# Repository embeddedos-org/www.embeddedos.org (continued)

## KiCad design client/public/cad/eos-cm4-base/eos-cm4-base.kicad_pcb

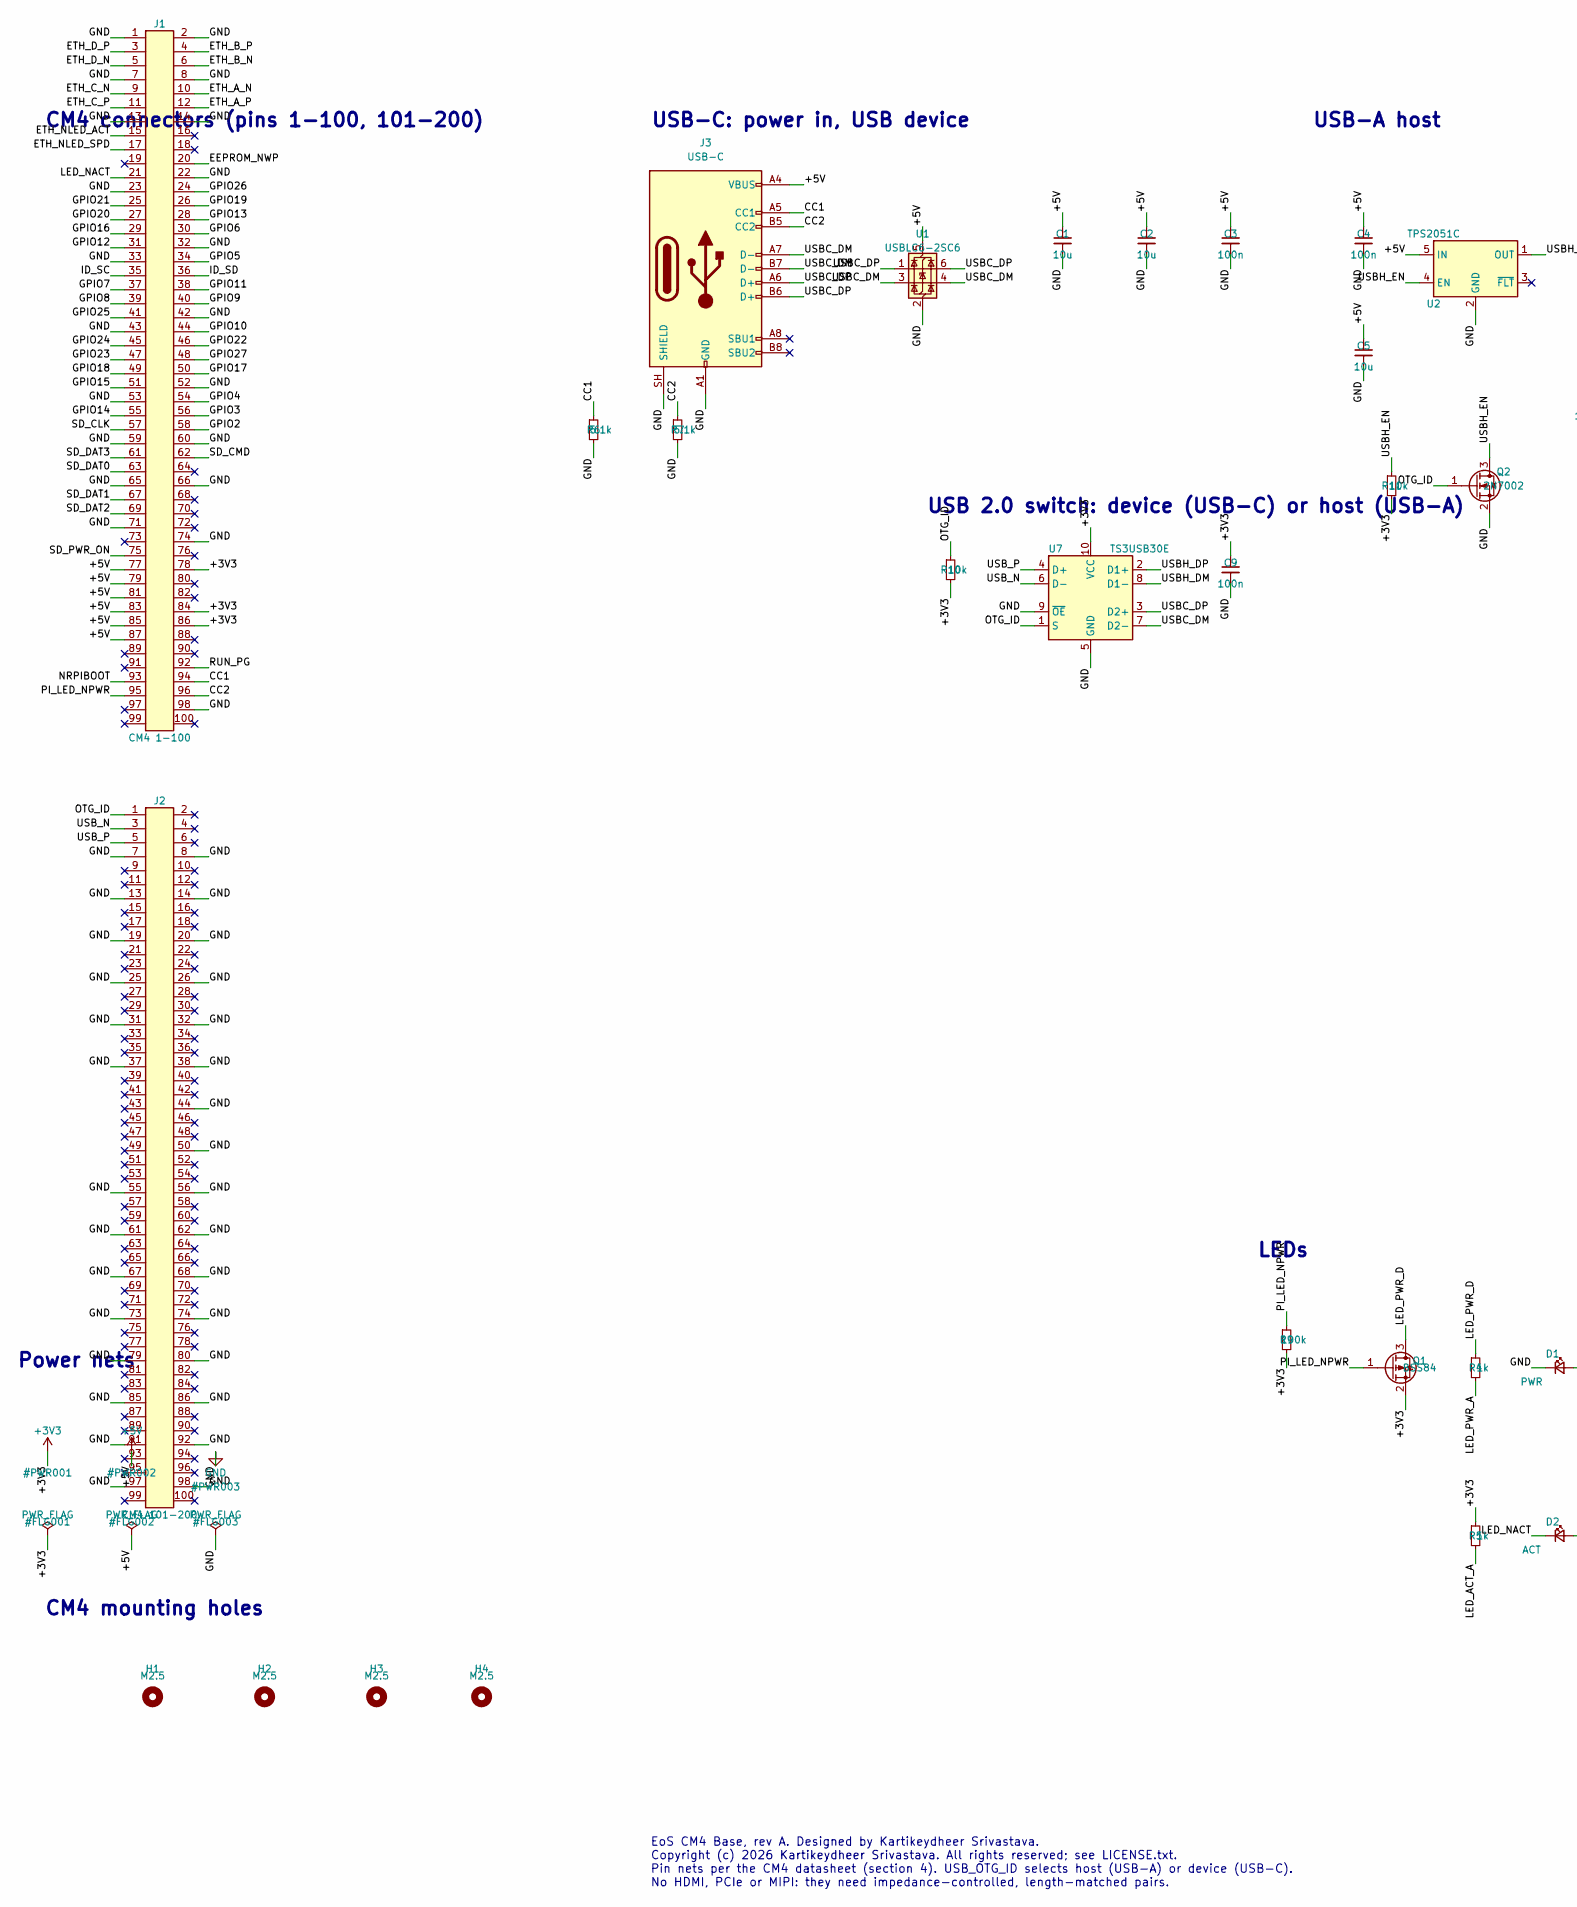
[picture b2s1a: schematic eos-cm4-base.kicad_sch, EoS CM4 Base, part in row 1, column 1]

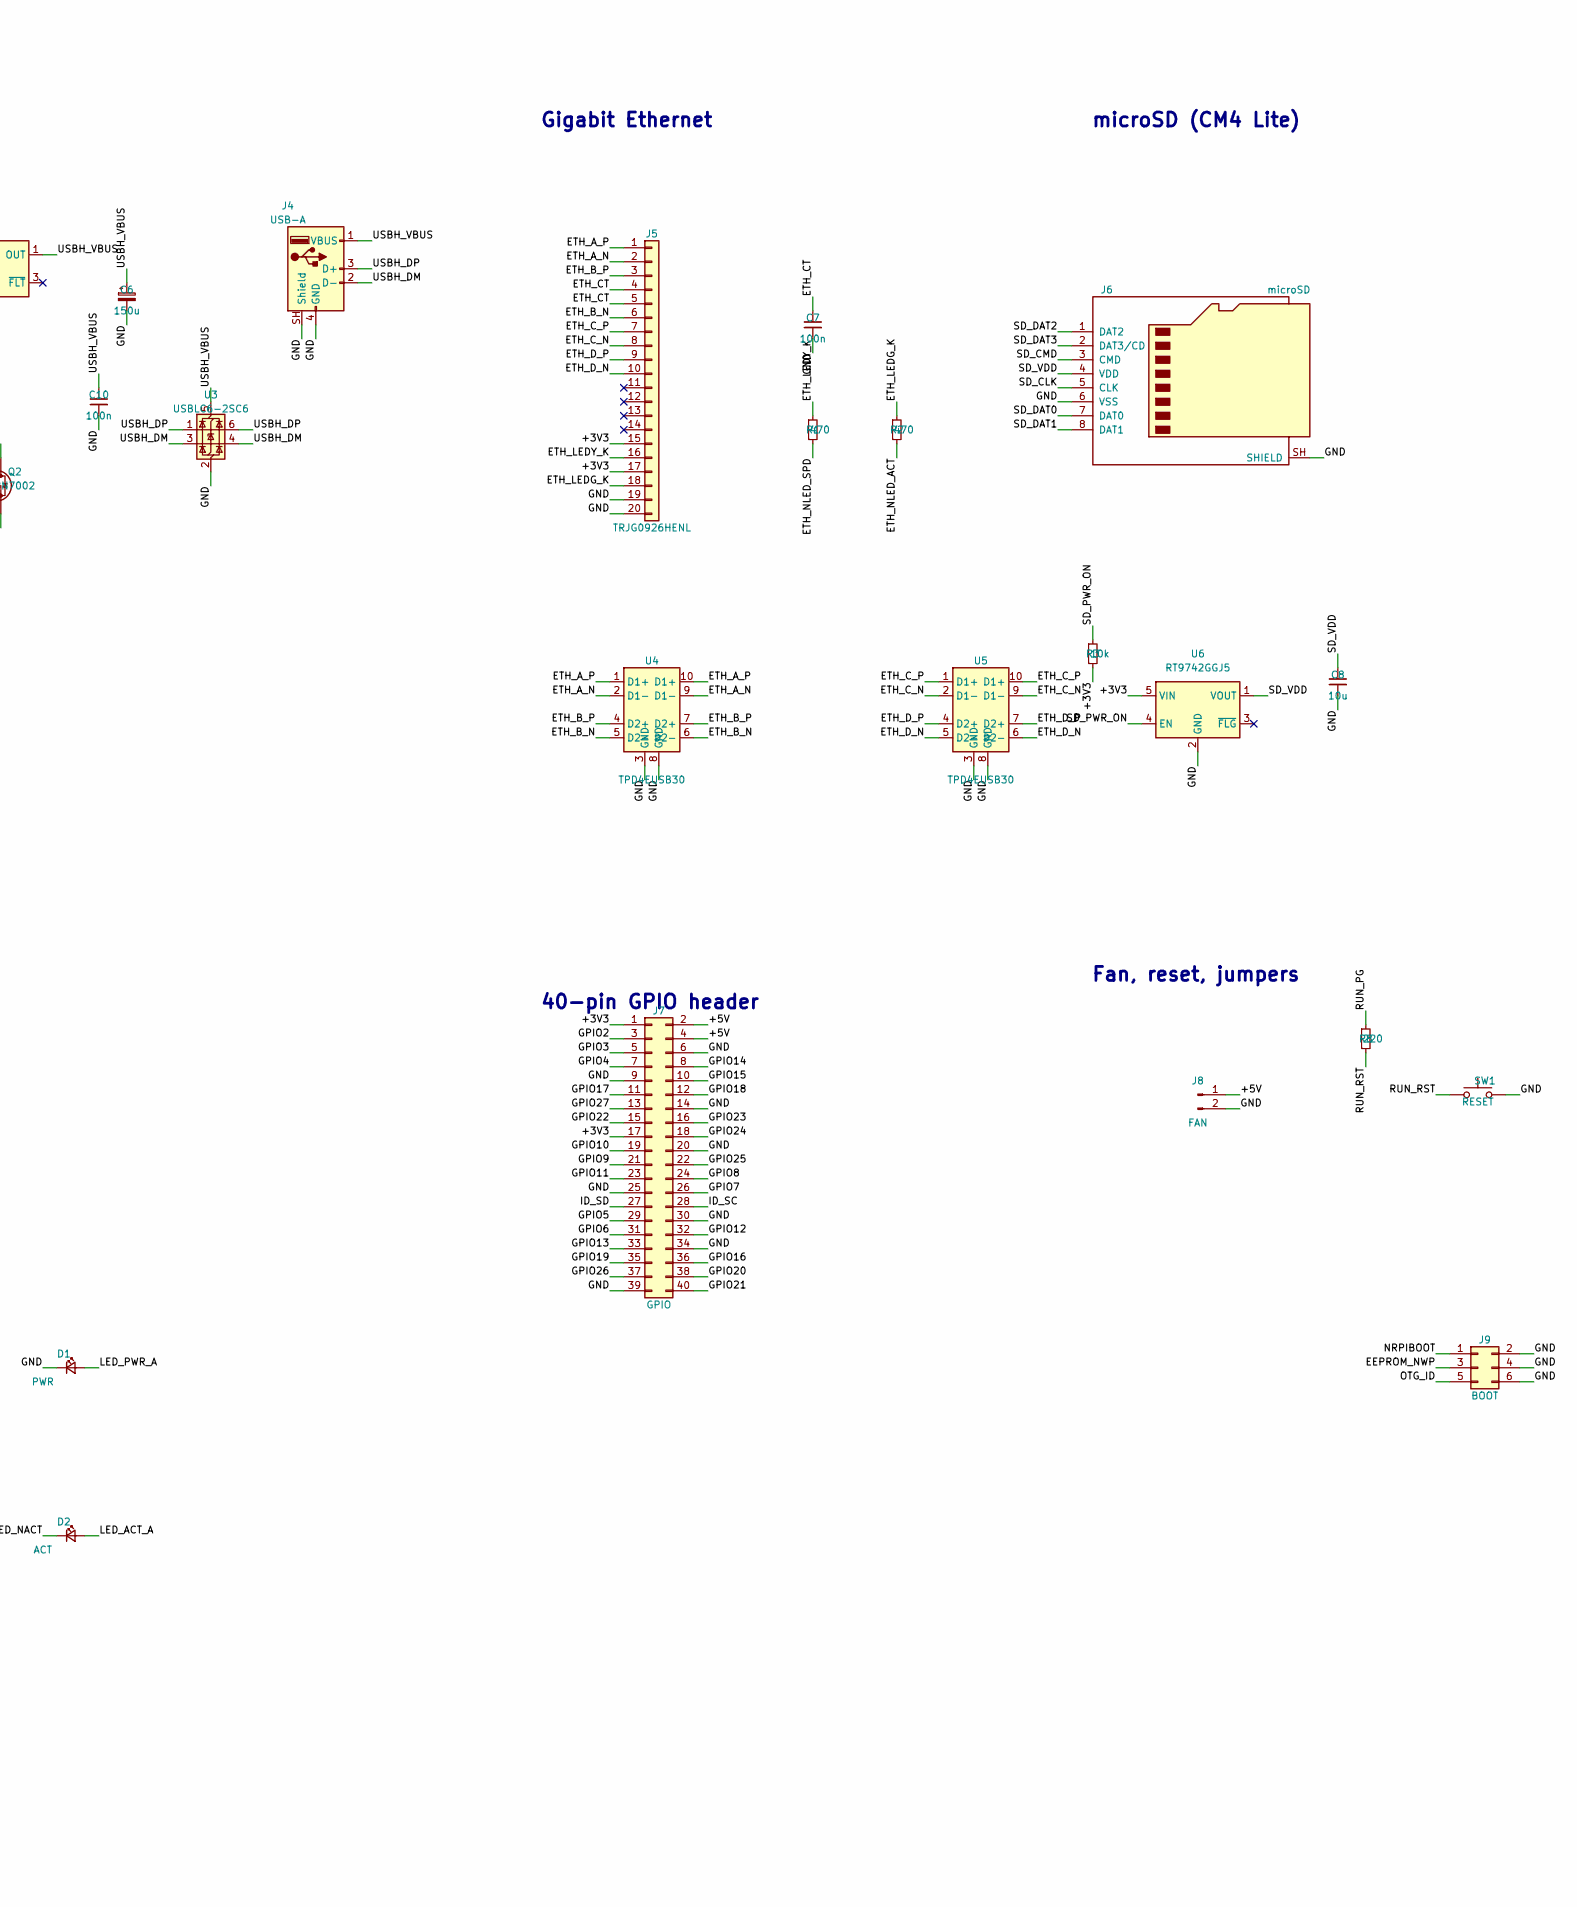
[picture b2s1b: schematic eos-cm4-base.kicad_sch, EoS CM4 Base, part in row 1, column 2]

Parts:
C1, C2, C5, C8: 10u; C_0805_2012Metric
C3, C4, C7, C9, C10: 100n; C_0402_1005Metric
C6: 150u; CP_Elec_6.3x5.8; MPN EEE-FK1A151P
D1: PWR; LED_0603_1608Metric; MPN APTD1608LSURCK
D2: ACT; LED_0603_1608Metric; MPN APTD1608LCGCK
H1, H2, H3, H4: M2.5; MountingHole_2.7mm_M2.5
J1: CM4 1-100; Hirose_DF40C-100DS-0.4V_2x50_P0.4mm; MPN DF40C-100DS-0.4V(51)
J2: CM4 101-200; Hirose_DF40C-100DS-0.4V_2x50_P0.4mm; MPN DF40C-100DS-0.4V(51)
J3: USB-C; USB_C_Receptacle_HRO_TYPE-C-31-M-12; MPN TYPE-C-31-M-12
J4: USB-A; USB_A_Molex_105057_Vertical; MPN 105057-0001
J5: TRJG0926HENL; TRXCOM_TRJG0926HENL; MPN TRJG0926HENL
J6: microSD; microSD_HC_Molex_104031-0811; MPN 104031-0811
J7: GPIO; PinHeader_2x20_P2.54mm_Vertical
J8: FAN; JST_SH_BM02B-SRSS-TB_1x02-1MP_P1.00mm_Vertical; MPN BM02B-SRSS-TB
J9: BOOT; PinHeader_2x03_P2.54mm_Vertical
Q1: BSS84; SOT-23; MPN BSS84,215
Q2: 2N7002; SOT-23; MPN 2N7002,215
R1, R2: 470; R_0402_1005Metric
R3, R10, R11: 10k; R_0402_1005Metric
R4, R5: 1k; R_0402_1005Metric
R6, R7: 5.1k; R_0402_1005Metric
R8: 220; R_0402_1005Metric
R9: 100k; R_0402_1005Metric
SW1: RESET; SW_Push_1P1T_NO_CK_KMR2; MPN KMR221G LFS
U1, U3: USBLC6-2SC6; SOT-23-6; MPN USBLC6-2SC6
U2: TPS2051C; SOT-23-5; MPN TPS2051CDBVR
U4, U5: TPD4EUSB30; USON-10_2.5x1.0mm_P0.5mm; MPN TPD4EUSB30DQAR
U6: RT9742GGJ5; TSOT-23-5; MPN RT9742GGJ5
U7: TS3USB30E; TSSOP-10_3x3mm_P0.5mm; MPN TS3USB30EDGSR

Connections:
+3V3: C9.1, J1.78, J1.84, J1.86, J5.15, J5.17, J7.1, J7.17, Q1.2 (S), R3.2, R5.1, R9.2, R10.2, R11.2, U6.5 (VIN), U7.10 (VCC)
+5V: C1.1, C2.1, C3.1, C4.1, C5.1, J1.77, J1.79, J1.81, J1.83, J1.85, J1.87, J3.A4 (VBUS), J3.A9 (VBUS), J3.B4 (VBUS), J3.B9 (VBUS), J7.2, J7.4, J8.1, U1.5 (VBUS), U2.5 (IN)
/CC1: J1.94, J3.A5 (CC1), R6.1
/CC2: J1.96, J3.B5 (CC2), R7.1
/EEPROM_NWP: J1.20, J9.3
/ETH_A_N: J1.10, J5.2, U4.2 (D1-), U4.9 (D1-)
/ETH_A_P: J1.12, J5.1, U4.1 (D1+), U4.10 (D1+)
/ETH_B_N: J1.6, J5.6, U4.5 (D2-), U4.6 (D2-)
/ETH_B_P: J1.4, J5.3, U4.4 (D2+), U4.7 (D2+)
/ETH_CT: C7.1, J5.4, J5.5
/ETH_C_N: J1.9, J5.8, U5.2 (D1-), U5.9 (D1-)
/ETH_C_P: J1.11, J5.7, U5.1 (D1+), U5.10 (D1+)
/ETH_D_N: J1.5, J5.10, U5.5 (D2-), U5.6 (D2-)
/ETH_D_P: J1.3, J5.9, U5.4 (D2+), U5.7 (D2+)
/ETH_LEDG_K: J5.18, R2.1
/ETH_LEDY_K: J5.16, R1.1
/ETH_NLED_ACT: J1.15, R2.2
/ETH_NLED_SPD: J1.17, R1.2
/GPIO2: J1.58, J7.3
/GPIO3: J1.56, J7.5
/GPIO4: J1.54, J7.7
/GPIO5: J1.34, J7.29
/GPIO6: J1.30, J7.31
/GPIO7: J1.37, J7.26
/GPIO8: J1.39, J7.24
/GPIO9: J1.40, J7.21
/GPIO10: J1.44, J7.19
/GPIO11: J1.38, J7.23
/GPIO12: J1.31, J7.32
/GPIO13: J1.28, J7.33
/GPIO14: J1.55, J7.8
/GPIO15: J1.51, J7.10
/GPIO16: J1.29, J7.36
/GPIO17: J1.50, J7.11
/GPIO18: J1.49, J7.12
/GPIO19: J1.26, J7.35
/GPIO20: J1.27, J7.38
/GPIO21: J1.25, J7.40
/GPIO22: J1.46, J7.15
/GPIO23: J1.47, J7.16
/GPIO24: J1.45, J7.18
/GPIO25: J1.41, J7.22
/GPIO26: J1.24, J7.37
/GPIO27: J1.48, J7.13
/ID_SC: J1.35, J7.28
/ID_SD: J1.36, J7.27
/LED_ACT_A: D2.2 (A), R5.2
/LED_NACT: D2.1 (K), J1.21
/LED_PWR_A: D1.2 (A), R4.2
/LED_PWR_D: Q1.3 (D), R4.1
/NRPIBOOT: J1.93, J9.1
/OTG_ID: J2.1, J9.5, Q2.1 (G), R10.1, U7.1 (S)
/PI_LED_NPWR: J1.95, Q1.1 (G), R9.1
/RUN_PG: J1.92, R8.1
/RUN_RST: R8.2, SW1.1
/SD_CLK: J1.57, J6.5 (CLK)
/SD_CMD: J1.62, J6.3 (CMD)
/SD_DAT0: J1.63, J6.7 (DAT0)
/SD_DAT1: J1.67, J6.8 (DAT1)
/SD_DAT2: J1.69, J6.1 (DAT2)
/SD_DAT3: J1.61, J6.2 (DAT3/CD)
/SD_PWR_ON: J1.75, R3.1, U6.4 (EN)
/SD_VDD: C8.1, J6.4 (VDD), U6.1 (VOUT)
/USBC_DM: J3.A7 (D-), J3.B7 (D-), U1.3 (I/O2), U1.4 (I/O2), U7.7 (D2-)
/USBC_DP: J3.A6 (D+), J3.B6 (D+), U1.1 (I/O1), U1.6 (I/O1), U7.3 (D2+)
/USBH_DM: J4.2 (D-), U3.3 (I/O2), U3.4 (I/O2), U7.8 (D1-)
/USBH_DP: J4.3 (D+), U3.1 (I/O1), U3.6 (I/O1), U7.2 (D1+)
/USBH_EN: Q2.3 (D), R11.1, U2.4 (EN)
/USBH_VBUS: C6.1, C10.1, J4.1 (VBUS), U2.1 (OUT), U3.5 (VBUS)
/USB_N: J2.3, U7.6 (D-)
/USB_P: J2.5, U7.4 (D+)
GND: C1.2, C2.2, C3.2, C4.2, C5.2, C6.2, C7.2, C8.2, C9.2, C10.2, D1.1 (K), J1.1, J1.2, J1.7, J1.8, J1.13, J1.14, J1.22, J1.23, J1.32, J1.33, J1.42, J1.43, J1.52, J1.53, J1.59, J1.60, J1.65, J1.66, J1.71, J1.74, J1.98, J2.7, J2.8, J2.13, J2.14, J2.19, J2.20, J2.25, J2.26, J2.31, J2.32, J2.37, J2.38, J2.44, J2.50, J2.55, J2.56, J2.61, J2.62, J2.67, J2.68, J2.73, J2.74, J2.79, J2.80, J2.85, J2.86, J2.91, J2.92, J2.97, J2.98, J3.A1 (GND), J3.A12 (GND), J3.B1 (GND), J3.B12 (GND), J3.SH (SHIELD), J4.4 (GND), J4.SH (Shield), J5.19, J5.20, J6.6 (VSS), J6.SH (SHIELD), J7.6, J7.9, J7.14, J7.20, J7.25, J7.30, J7.34, J7.39, J8.2, J9.2, J9.4, J9.6, Q2.2 (S), R6.2, R7.2, SW1.2, U1.2 (GND), U2.2 (GND), U3.2 (GND), U4.3 (GND), U4.8 (GND), U5.3 (GND), U5.8 (GND), U6.2 (GND), U7.5 (GND), U7.9 (~OE)

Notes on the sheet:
CM4 connectors (pins 1-100, 101-200)
USB-C: power in, USB device
USB 2.0 switch: device (USB-C) or host (USB-A)
USB-A host
Gigabit Ethernet
microSD (CM4 Lite)
40-pin GPIO header
Fan, reset, jumpers
LEDs
CM4 mounting holes
Power nets
EoS CM4 Base, rev A. Designed by Kartikeydheer Srivastava. Copyright (c) 2026 Kartikeydheer Srivastava. All rights reserved; see LICENSE.txt. Pin nets per the CM4 datasheet (section 4). USB_OTG_ID selects host (USB-A) or device (USB-C). No HDMI, PCIe or MIPI: they need impedance-controlled, length-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

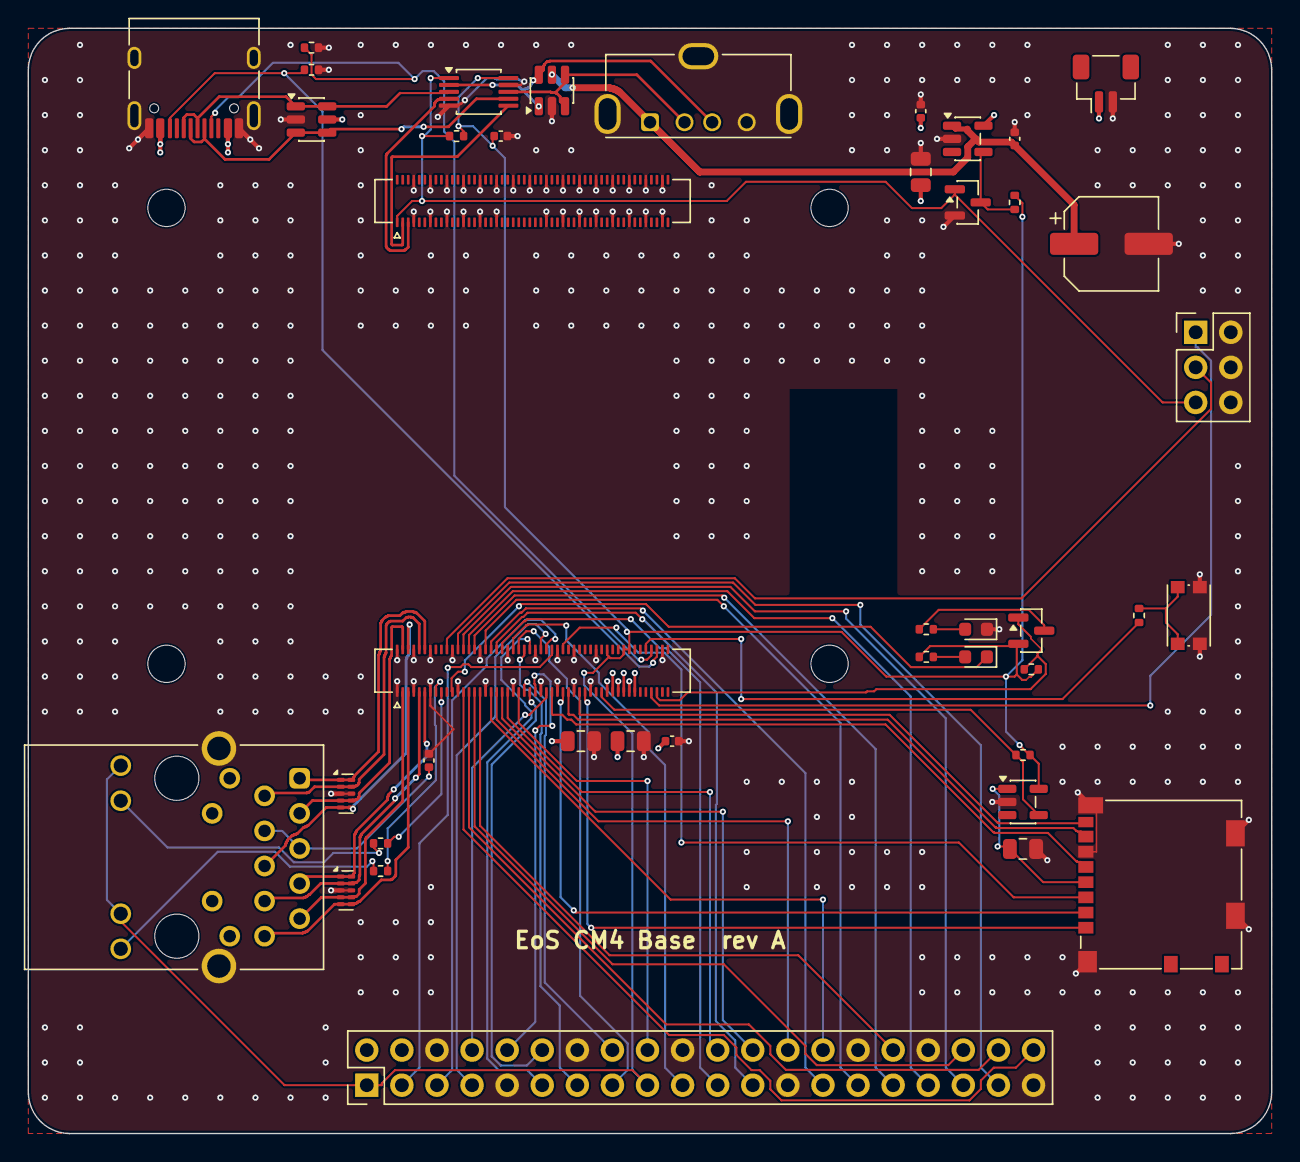
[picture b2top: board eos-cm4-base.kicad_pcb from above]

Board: 4 copper layers, 90.0 x 80.0 mm, 46 parts (0 on the bottom side), 72 nets.

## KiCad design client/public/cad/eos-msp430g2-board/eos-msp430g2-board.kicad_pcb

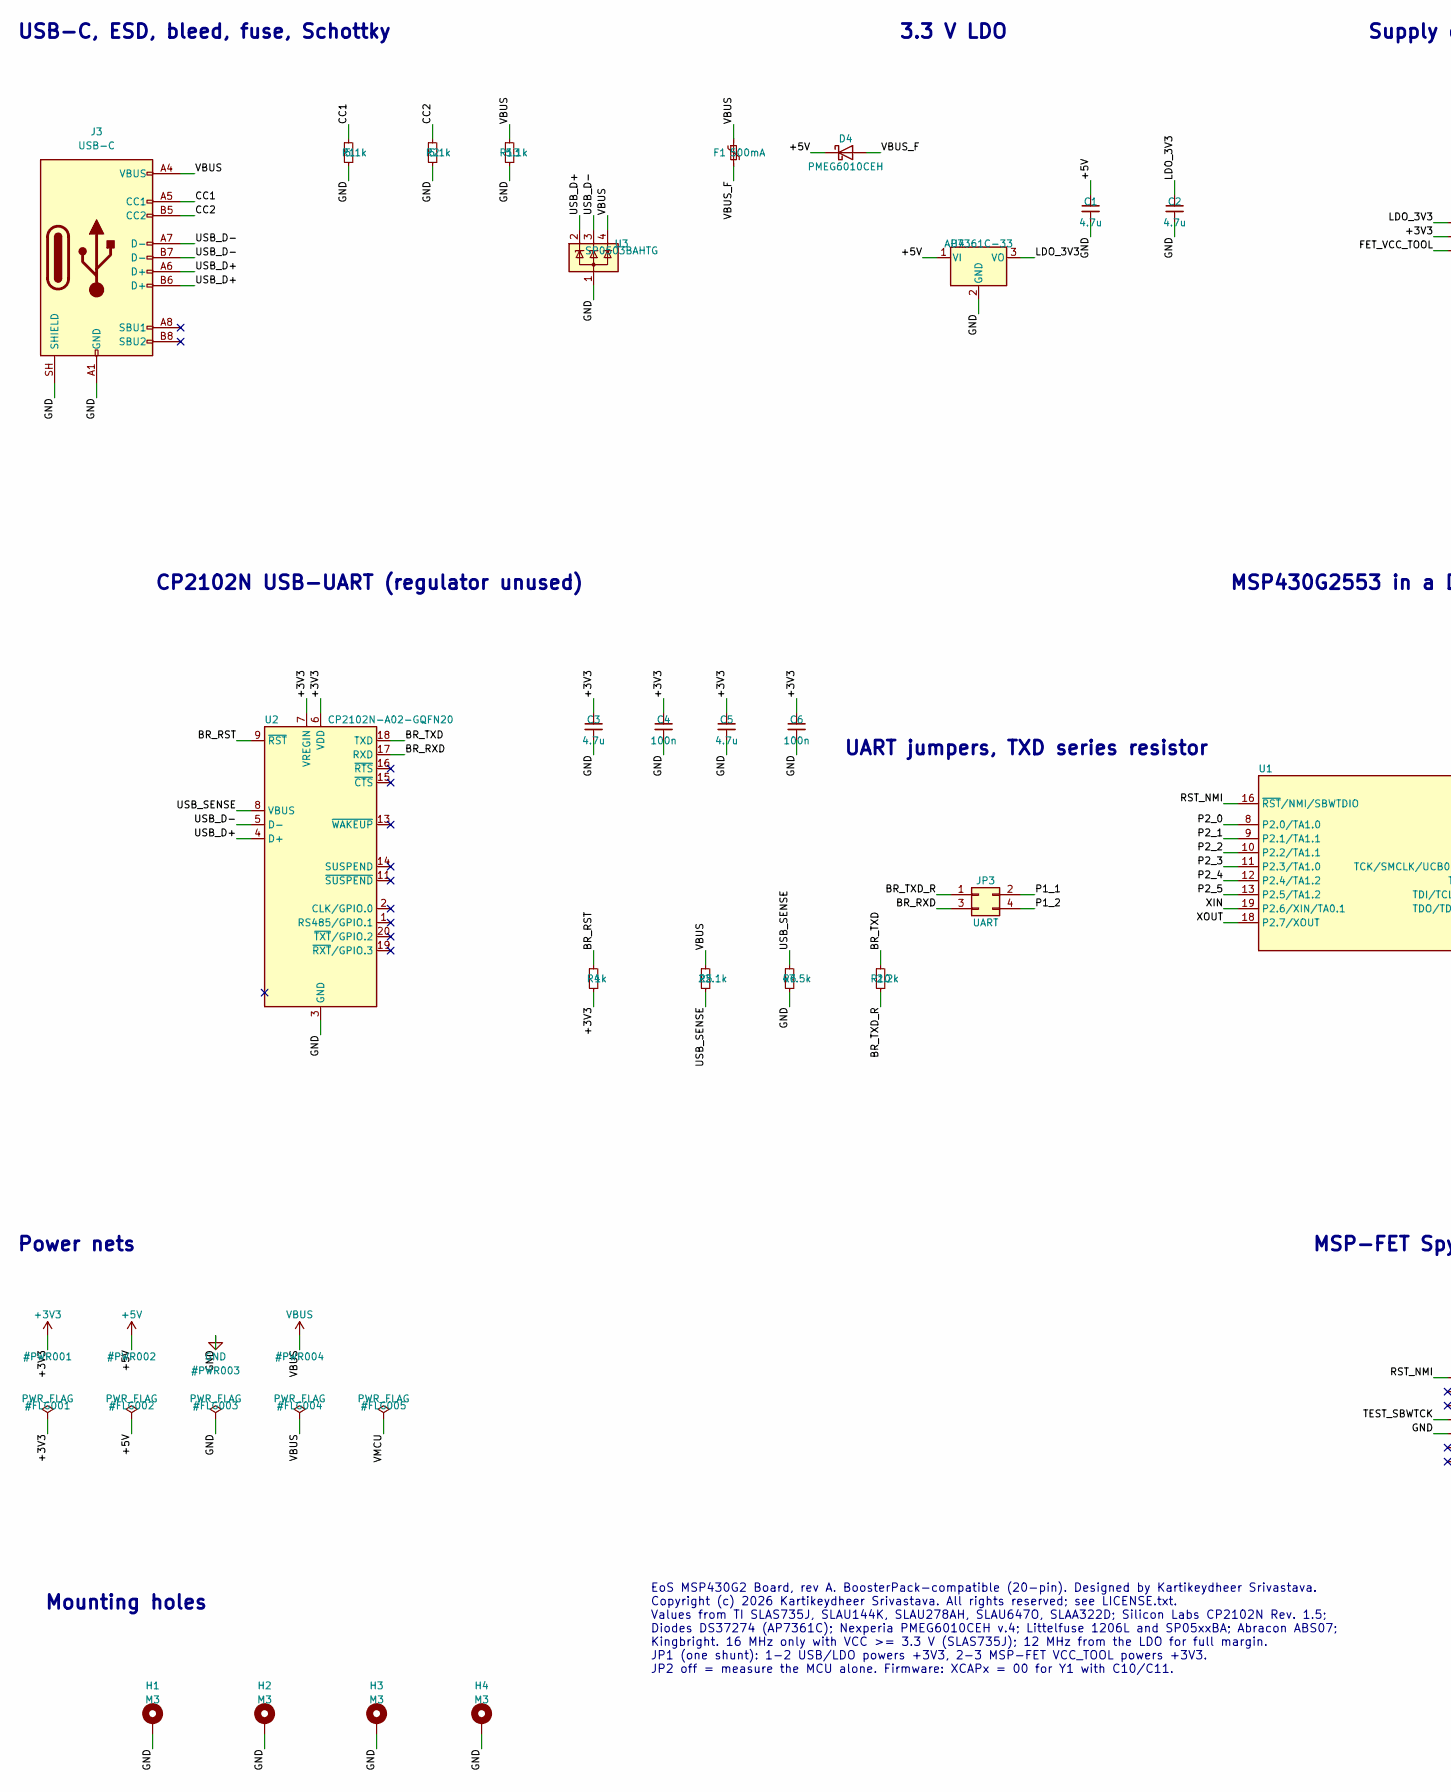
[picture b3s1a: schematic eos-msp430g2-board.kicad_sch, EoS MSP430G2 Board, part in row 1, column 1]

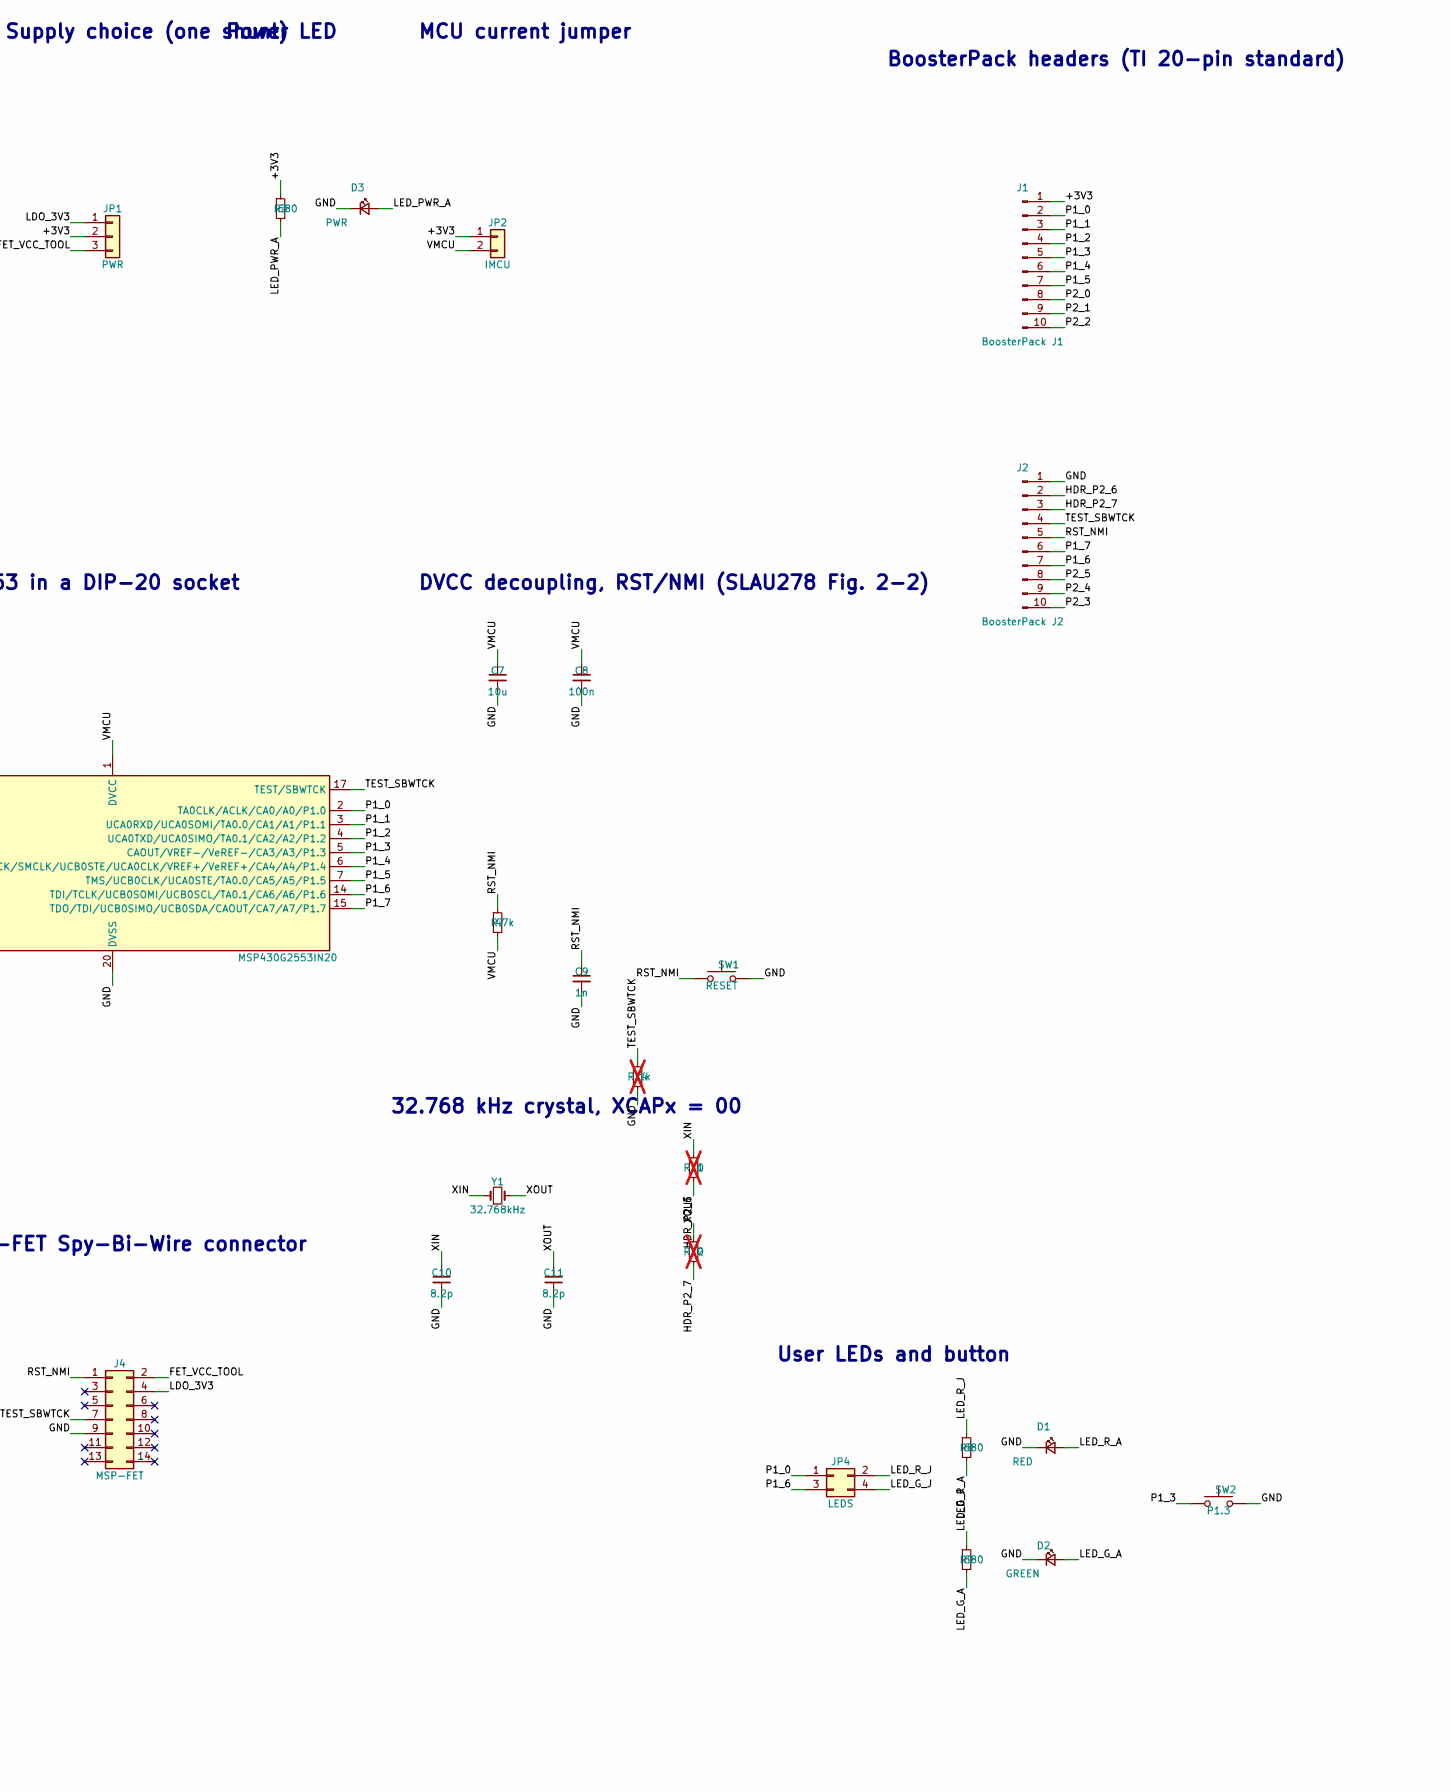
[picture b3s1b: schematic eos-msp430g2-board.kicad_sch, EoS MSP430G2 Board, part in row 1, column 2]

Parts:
C1, C2, C3, C5: 4.7u; C_0805_2012Metric
C4, C6, C8: 100n; C_0402_1005Metric
C7: 10u; C_0805_2012Metric
C9: 1n; C_0402_1005Metric; MPN GRM1555C1H102JA01D
C10, C11: 8.2p; C_0402_1005Metric; MPN GRM1555C1H8R2CA01D
D1: RED; LED_0603_1608Metric; MPN APTD1608LSURCK
D2: GREEN; LED_0603_1608Metric; MPN APTD1608LCGCK
D3: PWR; LED_0603_1608Metric; MPN APTD1608LSYCK
D4: PMEG6010CEH; D_SOD-123F; MPN PMEG6010CEH,115
F1: 500mA; Fuse_1206_3216Metric; MPN 1206L050YR
H1, H2, H3, H4: M3; MountingHole_3.2mm_M3_Pad_Via
J1: BoosterPack J1; PinHeader_1x10_P2.54mm_Vertical; MPN TSW-110-07-G-S
J2: BoosterPack J2; PinHeader_1x10_P2.54mm_Vertical; MPN TSW-110-07-G-S
J3: USB-C; USB_C_Receptacle_HRO_TYPE-C-31-M-12; MPN TYPE-C-31-M-12
J4: MSP-FET; IDC-Header_2x07_P2.54mm_Vertical; MPN 61201421621
JP1: PWR; PinHeader_1x03_P2.54mm_Vertical; MPN TSW-103-07-G-S
JP2: IMCU; PinHeader_1x02_P2.54mm_Vertical; MPN TSW-102-07-G-S
JP3: UART; PinHeader_2x02_P2.54mm_Vertical; MPN TSW-102-07-G-D
JP4: LEDS; PinHeader_2x02_P2.54mm_Vertical; MPN TSW-102-07-G-D
R1, R2, R13: 5.1k; R_0402_1005Metric
R3, R8, R9: 680; R_0402_1005Metric
R4: 1k; R_0402_1005Metric
R5: 22.1k; R_0402_1005Metric
R6: 47.5k; R_0402_1005Metric
R7: 47k; R_0402_1005Metric
R10: 2.2k; R_0402_1005Metric
R11, R12: 0; R_0402_1005Metric; not fitted
R14: 1k; R_0402_1005Metric; not fitted
SW1: RESET; SW_PUSH_6mm; MPN 1825910-6
SW2: P1.3; SW_PUSH_6mm; MPN 1825910-6
U1: MSP430G2553IN20; DIP-20_W7.62mm_Socket; MPN MSP430G2553IN20
U2: CP2102N-A02-GQFN20; SiliconLabs_QFN-20-1EP_3x3mm_P0.5mm_EP1.8x1.8mm; MPN CP2102N-A02-GQFN20R
U3: SP0503BAHTG; SOT-143; MPN SP0503BAHTG
U4: AP7361C-33; SOT-223-3_TabPin2; MPN AP7361C-33E-13
Y1: 32.768kHz; Crystal_SMD_3215-2Pin_3.2x1.5mm; MPN ABS07-32.768KHZ-6-T

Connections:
+3V3: C3.1, C4.1, C5.1, C6.1, J1.1, JP1.2, JP2.1, R3.1, R4.2, U2.6 (VDD), U2.7 (VREGIN)
+5V: C1.1, D4.1 (K), U4.1 (VI)
/BR_RST: R4.1, U2.9 (~RST)
/BR_RXD: JP3.3, U2.17 (RXD)
/BR_TXD: R10.1, U2.18 (TXD)
/BR_TXD_R: JP3.1, R10.2
/CC1: J3.A5 (CC1), R1.1
/CC2: J3.B5 (CC2), R2.1
/FET_VCC_TOOL: J4.2, JP1.3
/HDR_P2_6: J2.2, R11.2
/HDR_P2_7: J2.3, R12.2
/LDO_3V3: C2.1, J4.4, JP1.1, U4.3 (VO)
/LED_G_A: D2.2 (A), R9.2
/LED_G_J: JP4.4, R9.1
/LED_PWR_A: D3.2 (A), R3.2
/LED_R_A: D1.2 (A), R8.2
/LED_R_J: JP4.2, R8.1
/P1_0: J1.2, JP4.1, U1.2 (TA0CLK/ACLK/CA0/A0/P1.0)
/P1_1: J1.3, JP3.2, U1.3 (UCA0RXD/UCA0SOMI/TA0.0/CA1/A1/P1.1)
/P1_2: J1.4, JP3.4, U1.4 (UCA0TXD/UCA0SIMO/TA0.1/CA2/A2/P1.2)
/P1_3: J1.5, SW2.1, U1.5 (CAOUT/VREF-/VeREF-/CA3/A3/P1.3)
/P1_4: J1.6, U1.6 (TCK/SMCLK/UCB0STE/UCA0CLK/VREF+/VeREF+/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)
/P1_5: J1.7, U1.7 (TMS/UCB0CLK/UCA0STE/TA0.0/CA5/A5/P1.5)
/P1_6: J2.7, JP4.3, U1.14 (TDI/TCLK/UCB0SOMI/UCB0SCL/TA0.1/CA6/A6/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)
/P1_7: J2.6, U1.15 (TDO/TDI/UCB0SIMO/UCB0SDA/CAOUT/CA7/A7/P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)
/P2_0: J1.8, U1.8 (P2.0/TA1.0)
/P2_1: J1.9, U1.9 (P2.1/TA1.1)
/P2_2: J1.10, U1.10 (P2.2/TA1.1)
/P2_3: J2.10, U1.11 (P2.3/TA1.0)
/P2_4: J2.9, U1.12 (P2.4/TA1.2)
/P2_5: J2.8, U1.13 (P2.5/TA1.2)
/RST_NMI: C9.1, J2.5, J4.1, R7.1, SW1.1, U1.16 (~RST/NMI/SBWTDIO)
/TEST_SBWTCK: J2.4, J4.7, R14.1, U1.17 (TEST/SBWTCK)
/USB_D+: J3.A6 (D+), J3.B6 (D+), U2.4 (D+), U3.2 (K)
/USB_D-: J3.A7 (D-), J3.B7 (D-), U2.5 (D-), U3.3 (K)
/USB_SENSE: R5.2, R6.1, U2.8 (VBUS)
/VBUS_F: D4.2 (A), F1.2
/VMCU: C7.1, C8.1, JP2.2, R7.2, U1.1 (DVCC)
/XIN: C10.1, R11.1, U1.19 (P2.6/XIN/TA0.1), Y1.1
/XOUT: C11.1, R12.1, U1.18 (P2.7/XOUT), Y1.2
GND: C1.2, C2.2, C3.2, C4.2, C5.2, C6.2, C7.2, C8.2, C9.2, C10.2, C11.2, D1.1 (K), D2.1 (K), D3.1 (K), H1.1, H2.1, H3.1, H4.1, J2.1, J3.A1 (GND), J3.A12 (GND), J3.B1 (GND), J3.B12 (GND), J3.SH (SHIELD), J4.9, R1.2, R2.2, R6.2, R13.2, R14.2, SW1.2, SW2.2, U1.20 (DVSS), U2.3 (GND), U2.12 (GND), U2.21 (GND), U3.1 (A), U4.2 (GND)
VBUS: F1.1, J3.A4 (VBUS), J3.A9 (VBUS), J3.B4 (VBUS), J3.B9 (VBUS), R5.1, R13.1, U3.4 (K)

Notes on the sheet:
USB-C, ESD, bleed, fuse, Schottky
3.3 V LDO
Supply choice (one shunt)
Power LED
MCU current jumper
CP2102N USB-UART (regulator unused)
UART jumpers, TXD series resistor
MSP430G2553 in a DIP-20 socket
DVCC decoupling, RST/NMI (SLAU278 Fig. 2-2)
32.768 kHz crystal, XCAPx = 00
BoosterPack headers (TI 20-pin standard)
MSP-FET Spy-Bi-Wire connector
User LEDs and button
Mounting holes
Power nets
EoS MSP430G2 Board, rev A. BoosterPack-compatible (20-pin). Designed by Kartikeydheer Srivastava. Copyright (c) 2026 Kartikeydheer Srivastava. All rights reserved; see LICENSE.txt. Values from TI SLAS735J, SLAU144K, SLAU278AH, SLAU647O, SLAA322D; Silicon Labs CP2102N Rev. 1.5; Diodes DS37274 (AP736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

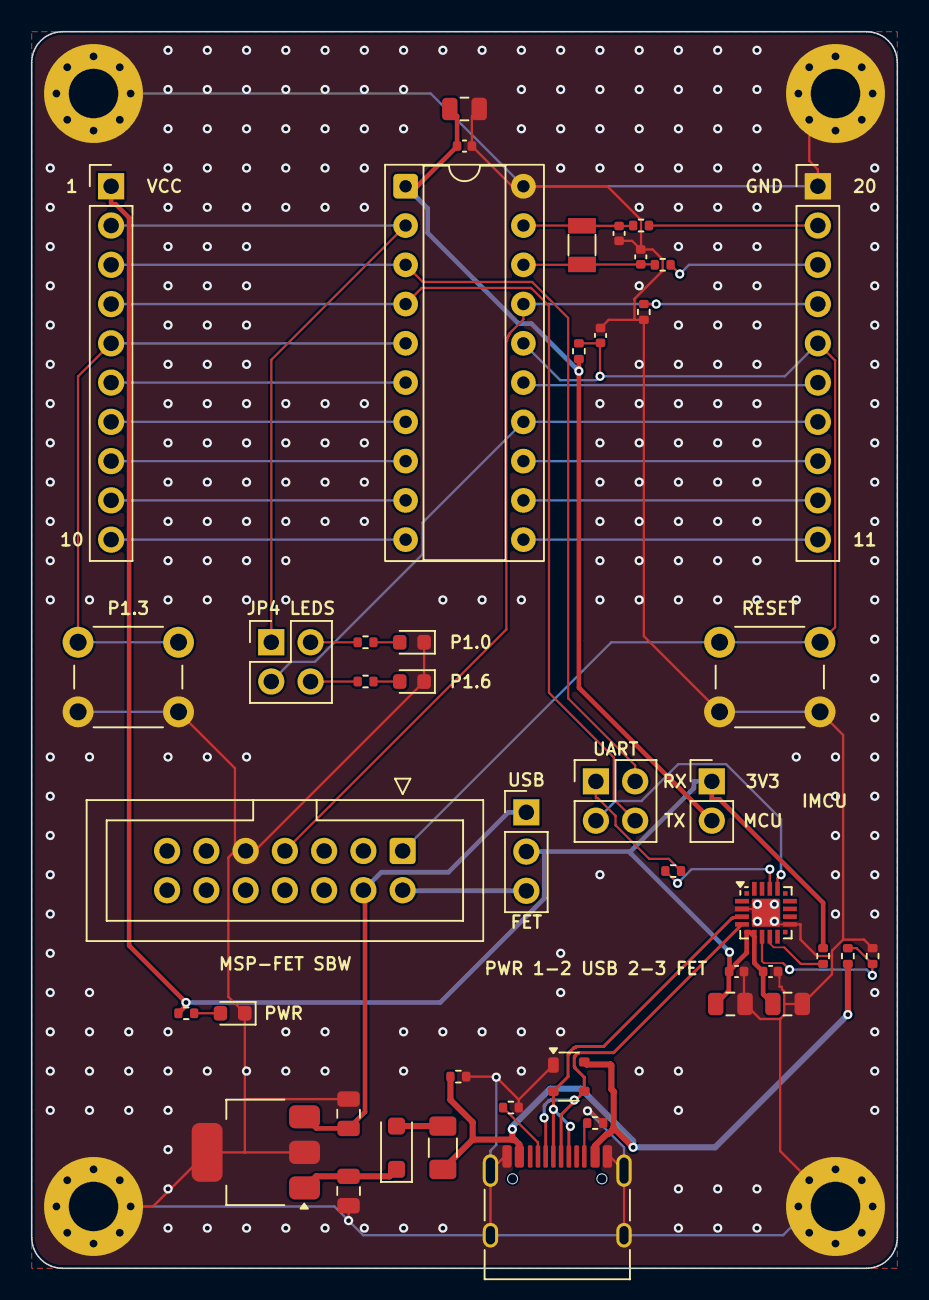
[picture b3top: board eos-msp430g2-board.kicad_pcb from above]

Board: 2 copper layers, 56.0 x 80.0 mm, 49 parts (0 on the bottom side), 42 nets.
